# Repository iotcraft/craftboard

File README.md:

# craftboard
An ESP32 based board designed to work with IoTCraft

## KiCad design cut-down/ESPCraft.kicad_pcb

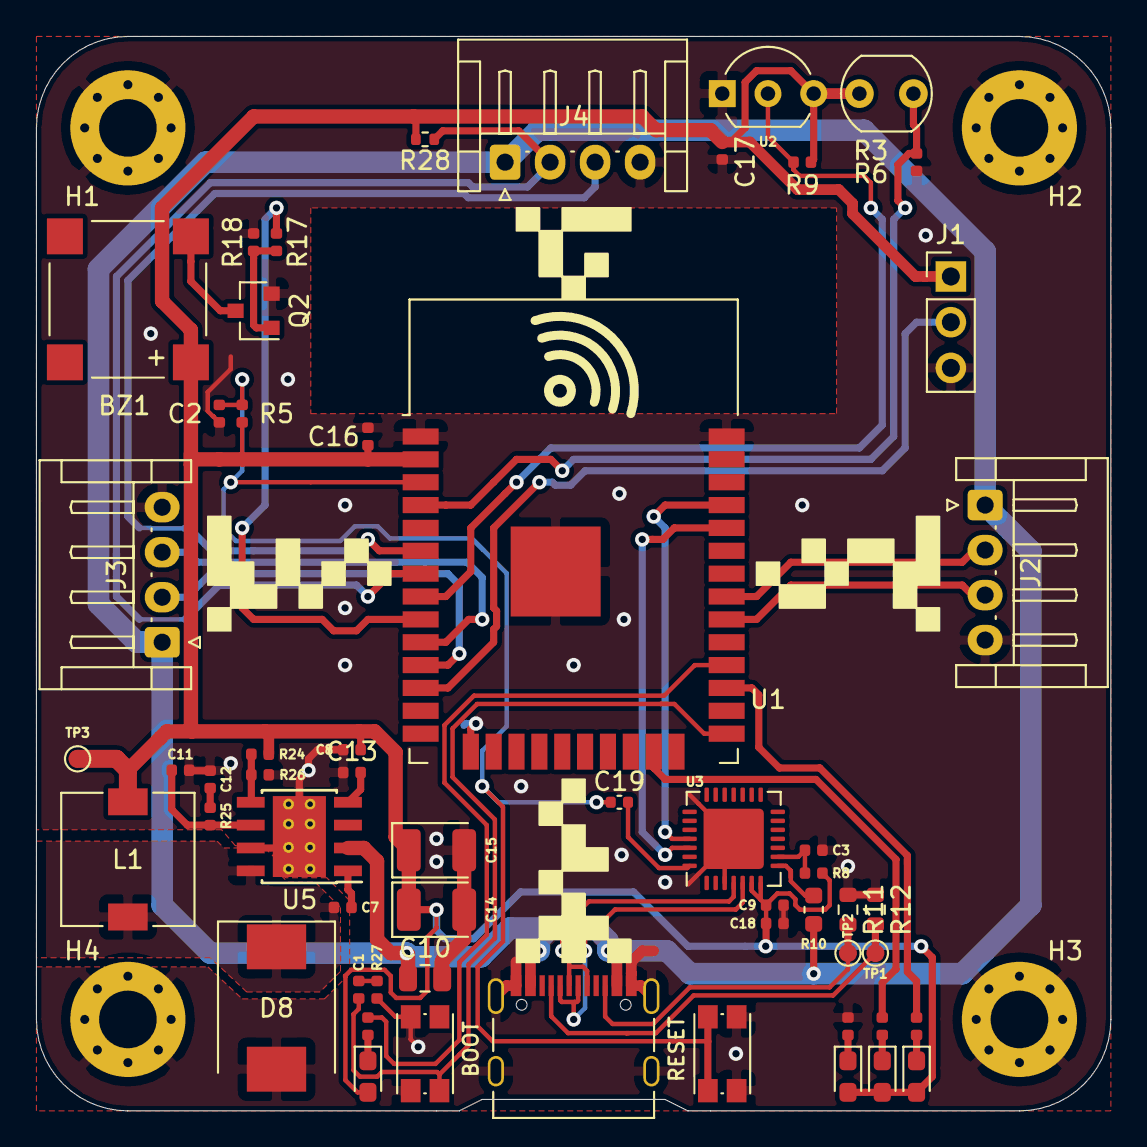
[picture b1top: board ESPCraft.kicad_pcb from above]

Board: 2 copper layers, 59.7 x 59.7 mm, 61 parts (0 on the bottom side), 40 nets.

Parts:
BZ1: Buzzer; PUIAudio_SMT_0825_S_4_R
C1, C16, C17, C18, C19: 100n; C_0402_1005Metric
C2, C3: 1u; C_0402_1005Metric
C7: 100n; R_0402_1005Metric
C8, C9: 4.7u; C_0402_1005Metric
C10: 22u; C_0805_2012Metric
C11: 10p; R_0402_1005Metric
C12: 1n; R_0402_1005Metric
C13: 10n; R_0402_1005Metric
C14, C15: 100u; CP_EIA-3528-15_AVX-H
D1: PWR; LED_0603_1608Metric_Pad1.05x0.95mm_HandSolder
D2: WIFI; LED_0603_1608Metric_Pad1.05x0.95mm_HandSolder
D3: ERROR; LED_0603_1608Metric_Pad1.05x0.95mm_HandSolder
D4: USR B; LED_0603_1608Metric_Pad1.05x0.95mm_HandSolder
D8: SS36-E3/57T; D_SMC
H1, H2, H3, H4: MountingHole; MountingHole_3.2mm_M3_Pad_Via
J1: LED_Matrix; PinHeader_1x03_P2.54mm_Vertical
J2, J3, J4: Redstone_wire; JST_EH_S4B-EH_1x04_P2.50mm_Horizontal
J5: USB_C_Receptacle_USB2.0; USB_C_Receptacle_Palconn_UTC16-G
L1: 4.7u; L_7.3x7.3_H3.5
Q2: S8050; SOT-23
R1, R2, R4, R7: 330; R_0402_1005Metric
R3: GL5516; R_LDR_5.0x4.1mm_P3mm_Vertical
R5, R6, R8, R17, R28: 10k; R_0402_1005Metric
R9: 4k7; R_0402_1005Metric
R10: 820; R_0603_1608Metric
R11, R12: 5.1k; R_0603_1608Metric
R18: 100k; R_0402_1005Metric
R24: 10.2k; R_0402_1005Metric
R25: 22k; R_0402_1005Metric
R26: 3.24k; R_0402_1005Metric
R27: 1k; R_0402_1005Metric
RST1: SW_RST; SW_Push_1P1T_NO_CK_KMR2
TP1, TP2, TP3: TestPoint; TestPoint_Pad_D1.0mm
U1: ESP32-WROOM-32D; ESP32-WROOM-32
U2: DS18B20; TO-92_Inline_Wide
U3: CP2102N-GQFN28; QFN-28-1EP_5x5mm_P0.5mm_EP3.35x3.35mm
U5: TPS54331DR; TI_SO-PowerPAD-8_ThermalVias
USR1: SW_USR; SW_Push_1P1T_NO_CK_KMR2

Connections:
+3V3: BZ1.1, C8.1, C9.1, C14.1, C15.1, C16.1, C17.1, C18.1, D1.2, D2.2, D3.2, D4.2, J1.1, L1.2, R3.1, R5.2, R8.2, R9.1, R24.1, R28.2, TP3.1, U1.2, U2.3, U3.6, U3.7
/BUZZER: R17.1, U1.9
/CC1: J5.A5, R12.2, TP1.1
/CC2: J5.B5, R11.2, TP2.1
/D+: J5.A6, J5.B6, U3.4
/D-: J5.A7, J5.B7, U3.5
/DISP_DATA: J1.2, U1.12
/LIGHT: R3.2, R6.1, U1.4
/L_SCK: J3.3, U1.10
/L_SDA: J3.2, U1.11
/R_SCK: J2.3, U1.30
/R_SDA: J2.2, U1.31
/TEMP: R9.2, U1.8, U2.2
/UP_SCK: J4.3, U1.6
/UP_SDA: J4.2, R28.1, U1.7
/USB_RX: U1.35, U3.25
/USB_TX: U1.34, U3.26
/~BUTTON: C1.1, U1.25, USR1.2
/~E_LED: R4.2, U1.27
/~RST: C2.1, C19.1, R5.1, RST1.2, U1.3
/~U_LED: R7.2, U1.28
/~W_LED: R2.2, U1.23
GND: C2.2, C3.2, C8.2, C9.2, C10.2, C11.1, C12.1, C13.1, C14.2, C15.2, C16.2, C17.2, C18.2, D8.2, H1.1, H2.1, H3.1, H4.1, J1.3, J2.4, J3.4, J4.4, J5.A1, J5.A12, J5.B1, J5.B12, J5.S1, Q2.2, R1.2, R6.2, R11.1, R12.1, R18.2, R26.2, R27.1, RST1.1, U1.1, U1.15, U1.38, U1.39, U2.1, U3.3, U3.29, U5.7, U5.9, USR1.1
unnamed: BZ1.2, Q2.3
unnamed: C1.2, R27.2
unnamed: C3.1, R8.1, U3.9
unnamed: C7.1, D8.1, L1.1, U5.8
unnamed: C7.2, U5.1
unnamed: C11.2, R25.1, U5.6
unnamed: C12.2, R25.2
unnamed: C13.2, U5.4
unnamed: C19.2, U3.28
unnamed: D1.1, R1.1
unnamed: D2.1, R2.1
unnamed: D3.1, R4.1
unnamed: D4.1, R7.1
unnamed: Q2.1, R17.2, R18.1
unnamed: R10.1, U3.8
unnamed: R24.2, R26.1, U5.5
VBUS: C10.1, J2.1, J3.1, J4.1, J5.A4, J5.A9, J5.B4, J5.B9, R10.2, U5.2

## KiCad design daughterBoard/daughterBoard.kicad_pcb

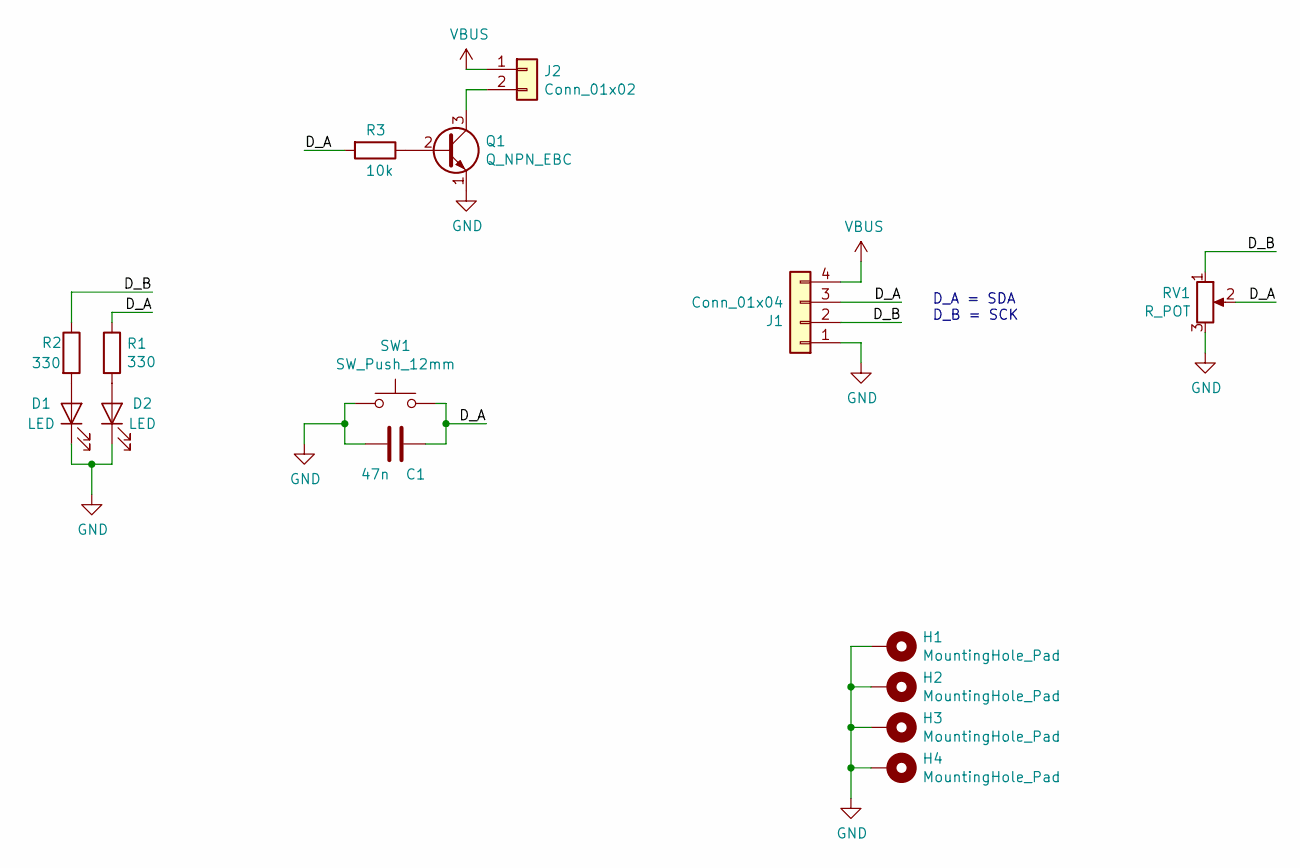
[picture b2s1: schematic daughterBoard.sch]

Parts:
C1: 47n; C_Disc_D5.0mm_W2.5mm_P5.00mm
D1, D2: LED; LED_D5.0mm
H1, H2, H3, H4: MountingHole_Pad; MountingHole_3.2mm_M3_Pad_Via
J1: Conn_01x04; JST_EH_S4B-EH_1x04_P2.50mm_Horizontal
J2: Conn_01x02; PinHeader_1x02_P2.54mm_Horizontal
Q1: Q_NPN_EBC; TO-92_Inline_Wide
R1, R2: 330; R_Axial_DIN0207_L6.3mm_D2.5mm_P2.54mm_Vertical
R3: 10k; R_Axial_DIN0207_L6.3mm_D2.5mm_P2.54mm_Vertical
RV1: R_POT; Potentiometer_Piher_T-16H_Single_Horizontal
SW1: SW_Push_12mm; SW_PUSH-12mm

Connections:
/D_A: C1.1, J1.3, R1.1, R3.2, RV1.2, SW1.2
/D_B: J1.2, R2.1, RV1.1
GND: C1.2, D1.1 (K), D2.1 (K), H1.1, H2.1, H3.1, H4.1, J1.1, Q1.1 (E), RV1.3, SW1.1
unnamed: D1.2 (A), R2.2
unnamed: D2.2 (A), R1.2
unnamed: J2.2, Q1.3 (C)
unnamed: Q1.2 (B), R3.1
VBUS: J1.4, J2.1

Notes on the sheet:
D_A = SDA D_B = SCK

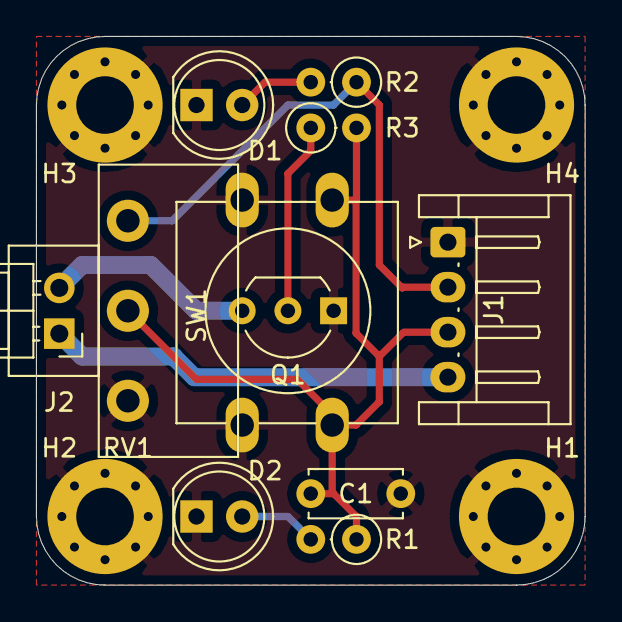
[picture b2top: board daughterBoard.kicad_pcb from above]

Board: 2 copper layers, 30.5 x 30.5 mm, 15 parts (0 on the bottom side), 8 nets.
